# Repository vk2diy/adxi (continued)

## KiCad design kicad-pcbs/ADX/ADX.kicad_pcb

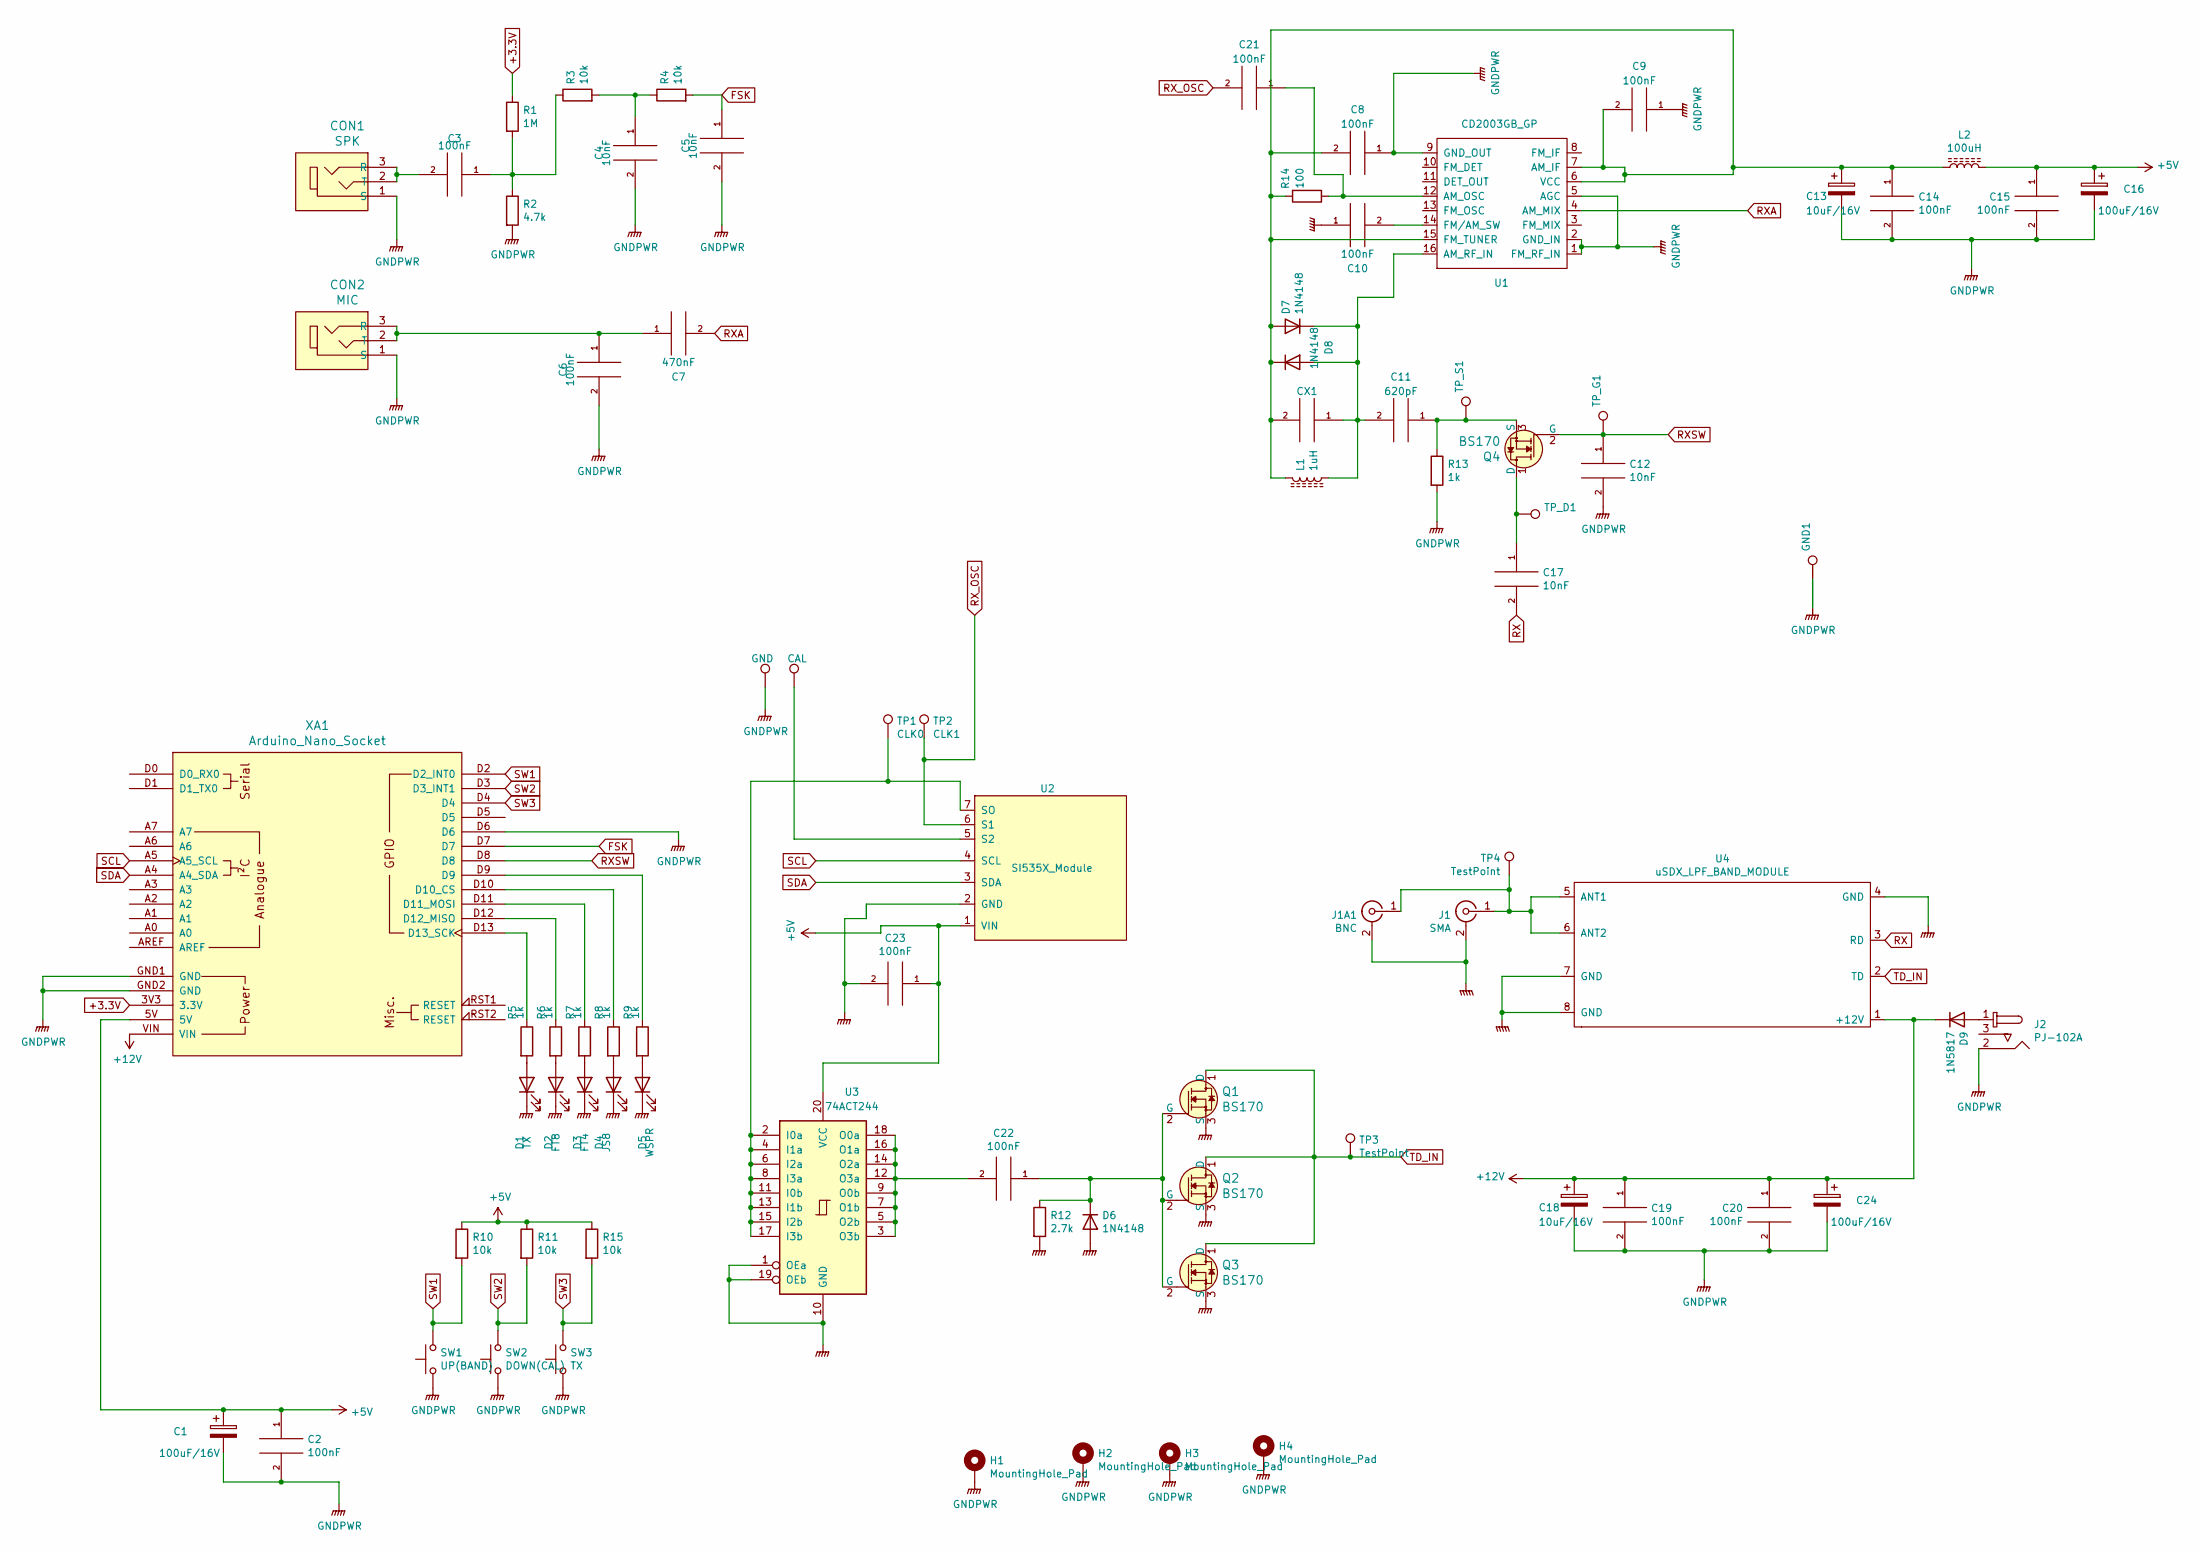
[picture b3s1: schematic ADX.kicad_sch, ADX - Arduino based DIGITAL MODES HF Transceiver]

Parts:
C1, C16, C24: 100uF/16V; CP_Radial_D5.0mm_P2.50mm
C2, C3, C6, C8, C9, C10, C14, C15, C19, C20, C21, C22, C23: 100nF; C_Disc_D3.0mm_W1.6mm_P2.50mm
C4, C5: 10nF; C_Disc_D3.0mm_W1.6mm_P2.50mm
C7: 470nF; C_Disc_D3.0mm_W1.6mm_P2.50mm
C11: 620pF; C_Disc_D3.0mm_W1.6mm_P2.50mm
C12, C17: 10nF; C_Disc_D3.0mm_W2.0mm_P2.50mm
C13, C18: 10uF/16V; CP_Radial_D5.0mm_P2.50mm
CON1: SPK; Headphone_Jack_3.5mm_SJ1-3523N; MPN SJ1-3523N; Digi-Key_PN CP1-3523N-ND
CON2: MIC; Headphone_Jack_3.5mm_SJ1-3523N; MPN SJ1-3523N; Digi-Key_PN CP1-3523N-ND
CX1: C_Disc_D3.0mm_W1.6mm_P2.50mm
D1: TX; LED_D3.0mm
D2: FT8; LED_D3.0mm
D3: FT4; LED_D3.0mm
D4: JS8; LED_D3.0mm
D5: WSPR; LED_D3.0mm
D6: 1N4148; D_A-405_P2.54mm_Vertical_AnodeUp
D7, D8: 1N4148; D_A-405_P2.54mm_Vertical_KathodeUp
D9: 1N5817; D_A-405_P2.54mm_Vertical_KathodeUp
GND1: TestPoint_THTPad_2.0x2.0mm_Drill1.0mm
H1, H2, H3, H4: MountingHole_Pad; MountingHole_3.2mm_M3_ISO7380_Pad
J1: SMA; SMA_Samtec_SMA-J-P-X-ST-EM1_EdgeMount
J1A1: BNC; BNC_Amphenol_B6252HB-NPP3G-50_Horizontal
J2: PJ-102A; Barrel_Jack_5.5mmODx2.1mmID_PJ-102A; MPN PJ-102A; Digi-Key_PN CP-102A-ND
L1: 1uH; L_Toroid_Vertical_L10.0mm_W5.0mm_P5.08mm
L2: 100uH; R_Axial_DIN0204_L3.6mm_D1.6mm_P2.54mm_Vertical
Q1, Q2, Q3: BS170; TO-92_HandSolder; MPN BS170; Digi-Key_PN BS170-ND
Q4: BS170; TO-92L_HandSolder; MPN BS170; Digi-Key_PN BS170-ND
R1: 1M; R_Axial_DIN0204_L3.6mm_D1.6mm_P1.90mm_Vertical
R2: 4.7k; R_Axial_DIN0204_L3.6mm_D1.6mm_P1.90mm_Vertical
R3, R4, R10, R11, R15: 10k; R_Axial_DIN0204_L3.6mm_D1.6mm_P1.90mm_Vertical
R5, R6, R7, R8, R9, R13: 1k; R_Axial_DIN0204_L3.6mm_D1.6mm_P1.90mm_Vertical
R12: 2.7k; R_Axial_DIN0204_L3.6mm_D1.6mm_P1.90mm_Vertical
R14: 100; R_Axial_DIN0204_L3.6mm_D1.6mm_P1.90mm_Vertical
SW1: UP(BAND); SW_PUSH_6mm
SW2: DOWN(CAL); SW_PUSH_6mm
SW3: TX; SW_PUSH_6mm
TP1: CLK0; TestPoint_THTPad_2.0x2.0mm_Drill1.0mm
TP2: CLK1; TestPoint_THTPad_2.0x2.0mm_Drill1.0mm
TP3, TP4: TestPoint; TestPoint_THTPad_2.0x2.0mm_Drill1.0mm
TP7: GND; TestPoint_THTPad_2.0x2.0mm_Drill1.0mm
TP8: CAL; TestPoint_THTPad_2.0x2.0mm_Drill1.0mm
TP_D1: TestPoint_THTPad_1.0x1.0mm_Drill0.5mm
TP_G1: TestPoint_THTPad_1.0x1.0mm_Drill0.5mm
TP_S1: TestPoint_THTPad_1.0x1.0mm_Drill0.5mm
U1: CD2003GB_GP; DIP-16_W7.62mm_Socket_LongPads
U2: SI535X_Module; SI5351 Module_Vertical
U3: 74ACT244; DIP-20_W7.62mm_LongPads
U4: uSDX_LPF_BAND_MODULE; uSDX_LPF_Band_Module
XA1: Arduino_Nano_Socket

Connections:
+3.3V: R1.1, XA1.3V3 (3.3V)
+5V: C1.1, C2.1, C15.1, C16.1, C23.1, L2.1, R10.1, R11.1, R15.1, U2.1 (VIN), U3.20 (VCC), XA1.5V
+12V: C18.1, C19.1, C20.1, C24.1, D9.1 (K), U4.1 (+12V), XA1.VIN
FSK: C5.1, R4.2, XA1.D7
GNDPWR: C1.2, C2.2, C4.2, C5.2, C6.2, C8.1, C9.1, C10.1, C12.2, C13.2, C14.2, C15.2, C16.2, C18.2, C19.2, C20.2, C23.2, C24.2, CON1.1 (S), CON2.1 (S), D1.1 (K), D2.1 (K), D3.1 (K), D4.1 (K), D5.1 (K), D6.2 (A), GND1.1, H1.1, H2.1, H3.1, H4.1, J1.2 (Ext), J1A1.2 (Ext), J2.2, Q1.3 (S), Q2.3 (S), Q3.3 (S), R2.2, R12.2, R13.2, SW1.1, SW2.1, SW3.1, TP7.1, U1.1 (FM_RF_IN), U1.2 (GND_IN), U1.5 (AGC), U1.9 (GND_OUT), U2.2 (GND), U3.1 (OEa), U3.10 (GND), U3.19 (OEb), U4.4 (GND), U4.7 (GND), U4.8 (GND), XA1.D6, XA1.GND1 (GND), XA1.GND2 (GND)
unnamed: C3.1, R1.2, R2.1, R3.1
unnamed: C3.2, CON1.2 (T), CON1.3 (R)
unnamed: C4.1, R3.2, R4.1
unnamed: C6.1, C7.1, CON2.2 (T), CON2.3 (R)
unnamed: C10.2, U1.14 (FM/AM_SW)
unnamed: C11.1, Q4.3 (S), R13.1, TP_S1.1
unnamed: C11.2, CX1.1, D7.1 (K), D8.2 (A), L1.1, U1.16 (AM_RF_IN)
unnamed: C8.2, C9.2, C13.1, C14.1, CX1.2, D7.2 (A), D8.1 (K), L1.2, L2.2, R14.2, U1.6 (VCC), U1.7 (AM_IF), U1.15 (FM_TUNER)
unnamed: C17.1, Q4.1 (D), TP_D1.1
unnamed: C21.1, R14.1, U1.12 (AM_OSC)
unnamed: C22.1, D6.1 (K), Q1.2 (G), Q2.2 (G), Q3.2 (G), R12.1
unnamed: C22.2, U3.3 (O3b), U3.5 (O2b), U3.7 (O1b), U3.9 (O0b), U3.12 (O3a), U3.14 (O2a), U3.16 (O1a), U3.18 (O0a)
unnamed: D1.2 (A), R5.2
unnamed: D2.2 (A), R6.2
unnamed: D3.2 (A), R7.2
unnamed: D4.2 (A), R8.2
unnamed: D5.2 (A), R9.2
unnamed: D9.2 (A), J2.1
unnamed: J1.1 (In), J1A1.1 (In), TP4.1, U4.5 (ANT1), U4.6 (ANT2)
unnamed: R5.1, XA1.D13 (D13_SCK)
unnamed: R6.1, XA1.D12 (D12_MISO)
unnamed: R7.1, XA1.D11 (D11_MOSI)
unnamed: R8.1, XA1.D10 (D10_CS)
unnamed: R9.1, XA1.D9
unnamed: TP1.1, U2.7 (SO), U3.2 (I0a), U3.4 (I1a), U3.6 (I2a), U3.8 (I3a), U3.11 (I0b), U3.13 (I1b), U3.15 (I2b), U3.17 (I3b)
unnamed: TP8.1, U2.5 (S2)
RX: C17.2, U4.3 (RD)
RXA: C7.2, U1.4 (AM_MIX)
RXSW: C12.1, Q4.2 (G), TP_G1.1, XA1.D8
RX_OSC: C21.2, TP2.1, U2.6 (S1)
SCL: U2.4 (SCL), XA1.A5 (A5_SCL)
SDA: U2.3 (SDA), XA1.A4 (A4_SDA)
SW1: R10.2, SW1.2, XA1.D2 (D2_INT0)
SW2: R11.2, SW2.2, XA1.D3 (D3_INT1)
SW3: R15.2, SW3.2, XA1.D4
TD_IN: Q1.1 (D), Q2.1 (D), Q3.1 (D), TP3.1, U4.2 (TD)

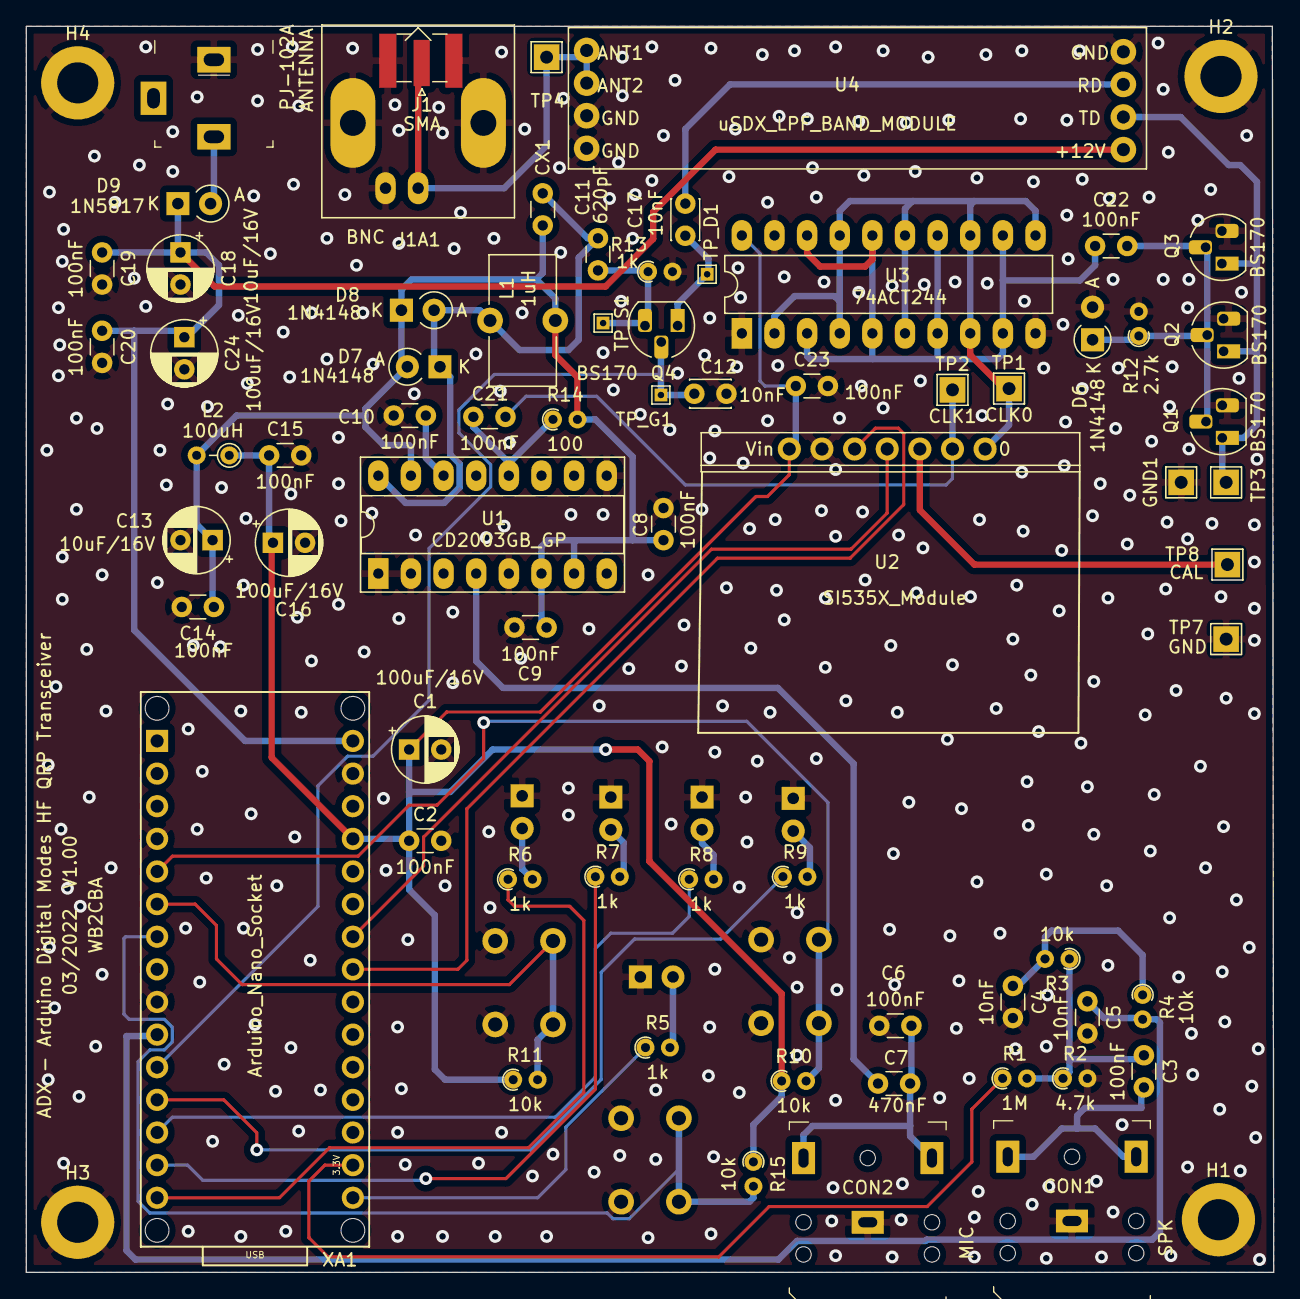
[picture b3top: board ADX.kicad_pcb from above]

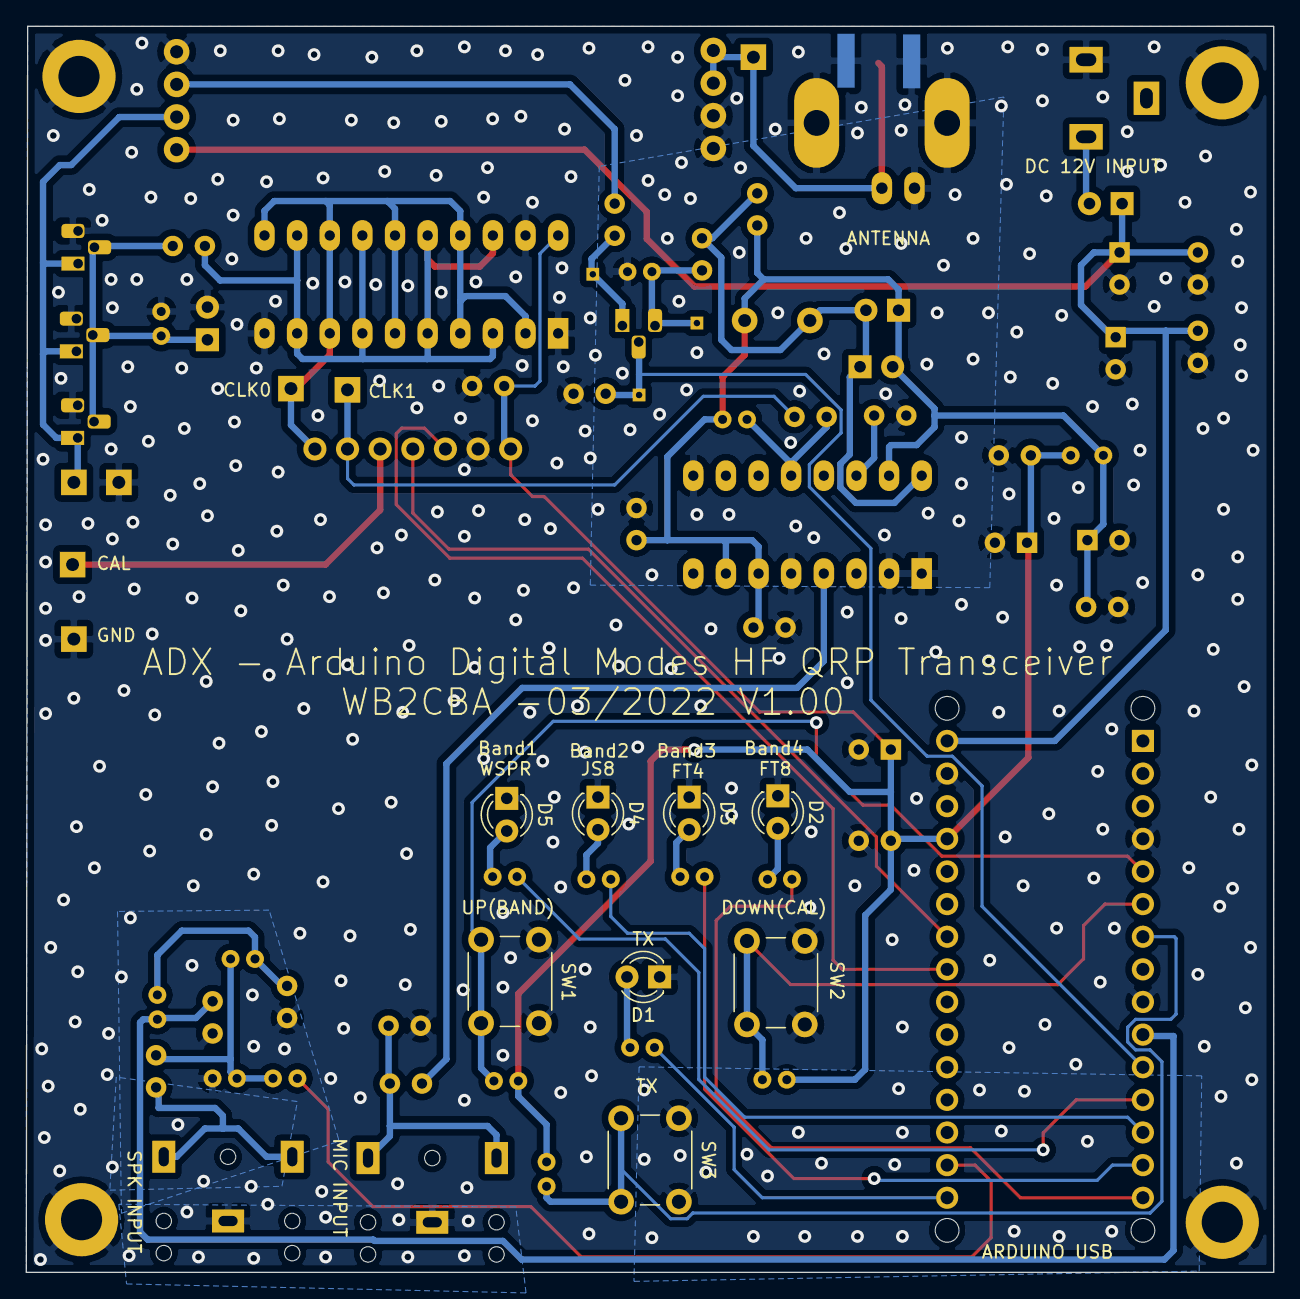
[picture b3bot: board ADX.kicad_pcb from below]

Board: 2 copper layers, 97.1 x 97.0 mm, 82 parts (8 on the bottom side), 41 nets.

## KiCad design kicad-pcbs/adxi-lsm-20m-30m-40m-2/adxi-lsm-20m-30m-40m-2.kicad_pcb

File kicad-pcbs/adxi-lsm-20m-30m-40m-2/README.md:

# adxi-lsm-20m-30m-40m-2

## Timeline

 * Conceived: 2024-10-01 or so
 * Designed: 2024-10-01 to 2024-10-24
   * Main design challenges were re-working existing designs coming out of [classe2-calculator](https://github.com/vk2diy/classe2-calculator)
   * The rework function `--equivalent-inductor` had to be authored and debugged
   * The reworked circuits are definitely better than the originals
 * Ordered: 2024-10-24
   * Cost: $17.80 for 20 boards + $98.70 for 20 boards assembly = $116.5 / 20 = $5.825 each
 * ETA: 2024-11-05 or so

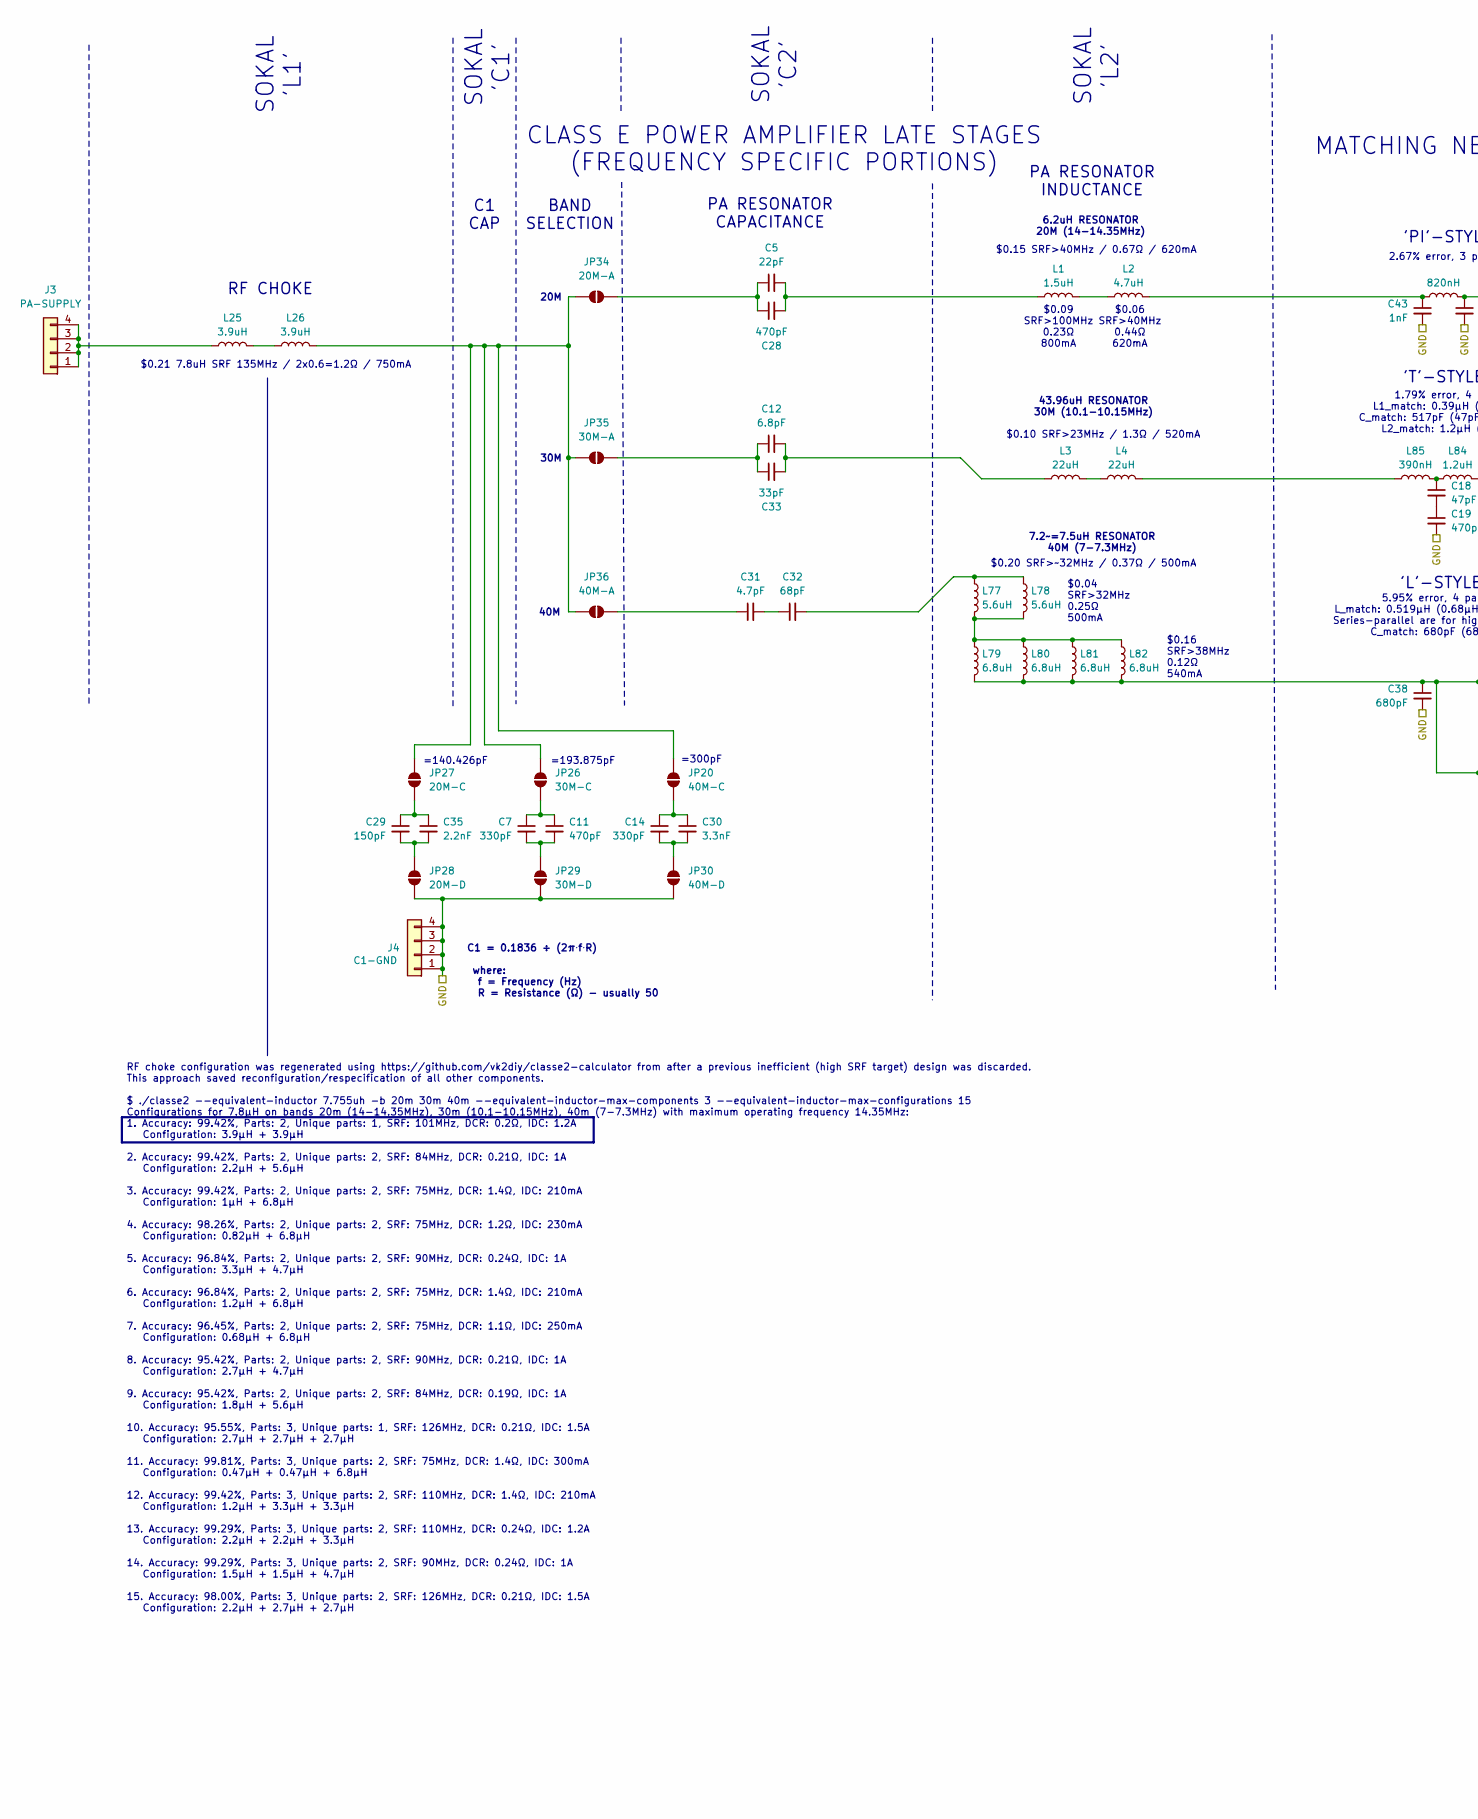
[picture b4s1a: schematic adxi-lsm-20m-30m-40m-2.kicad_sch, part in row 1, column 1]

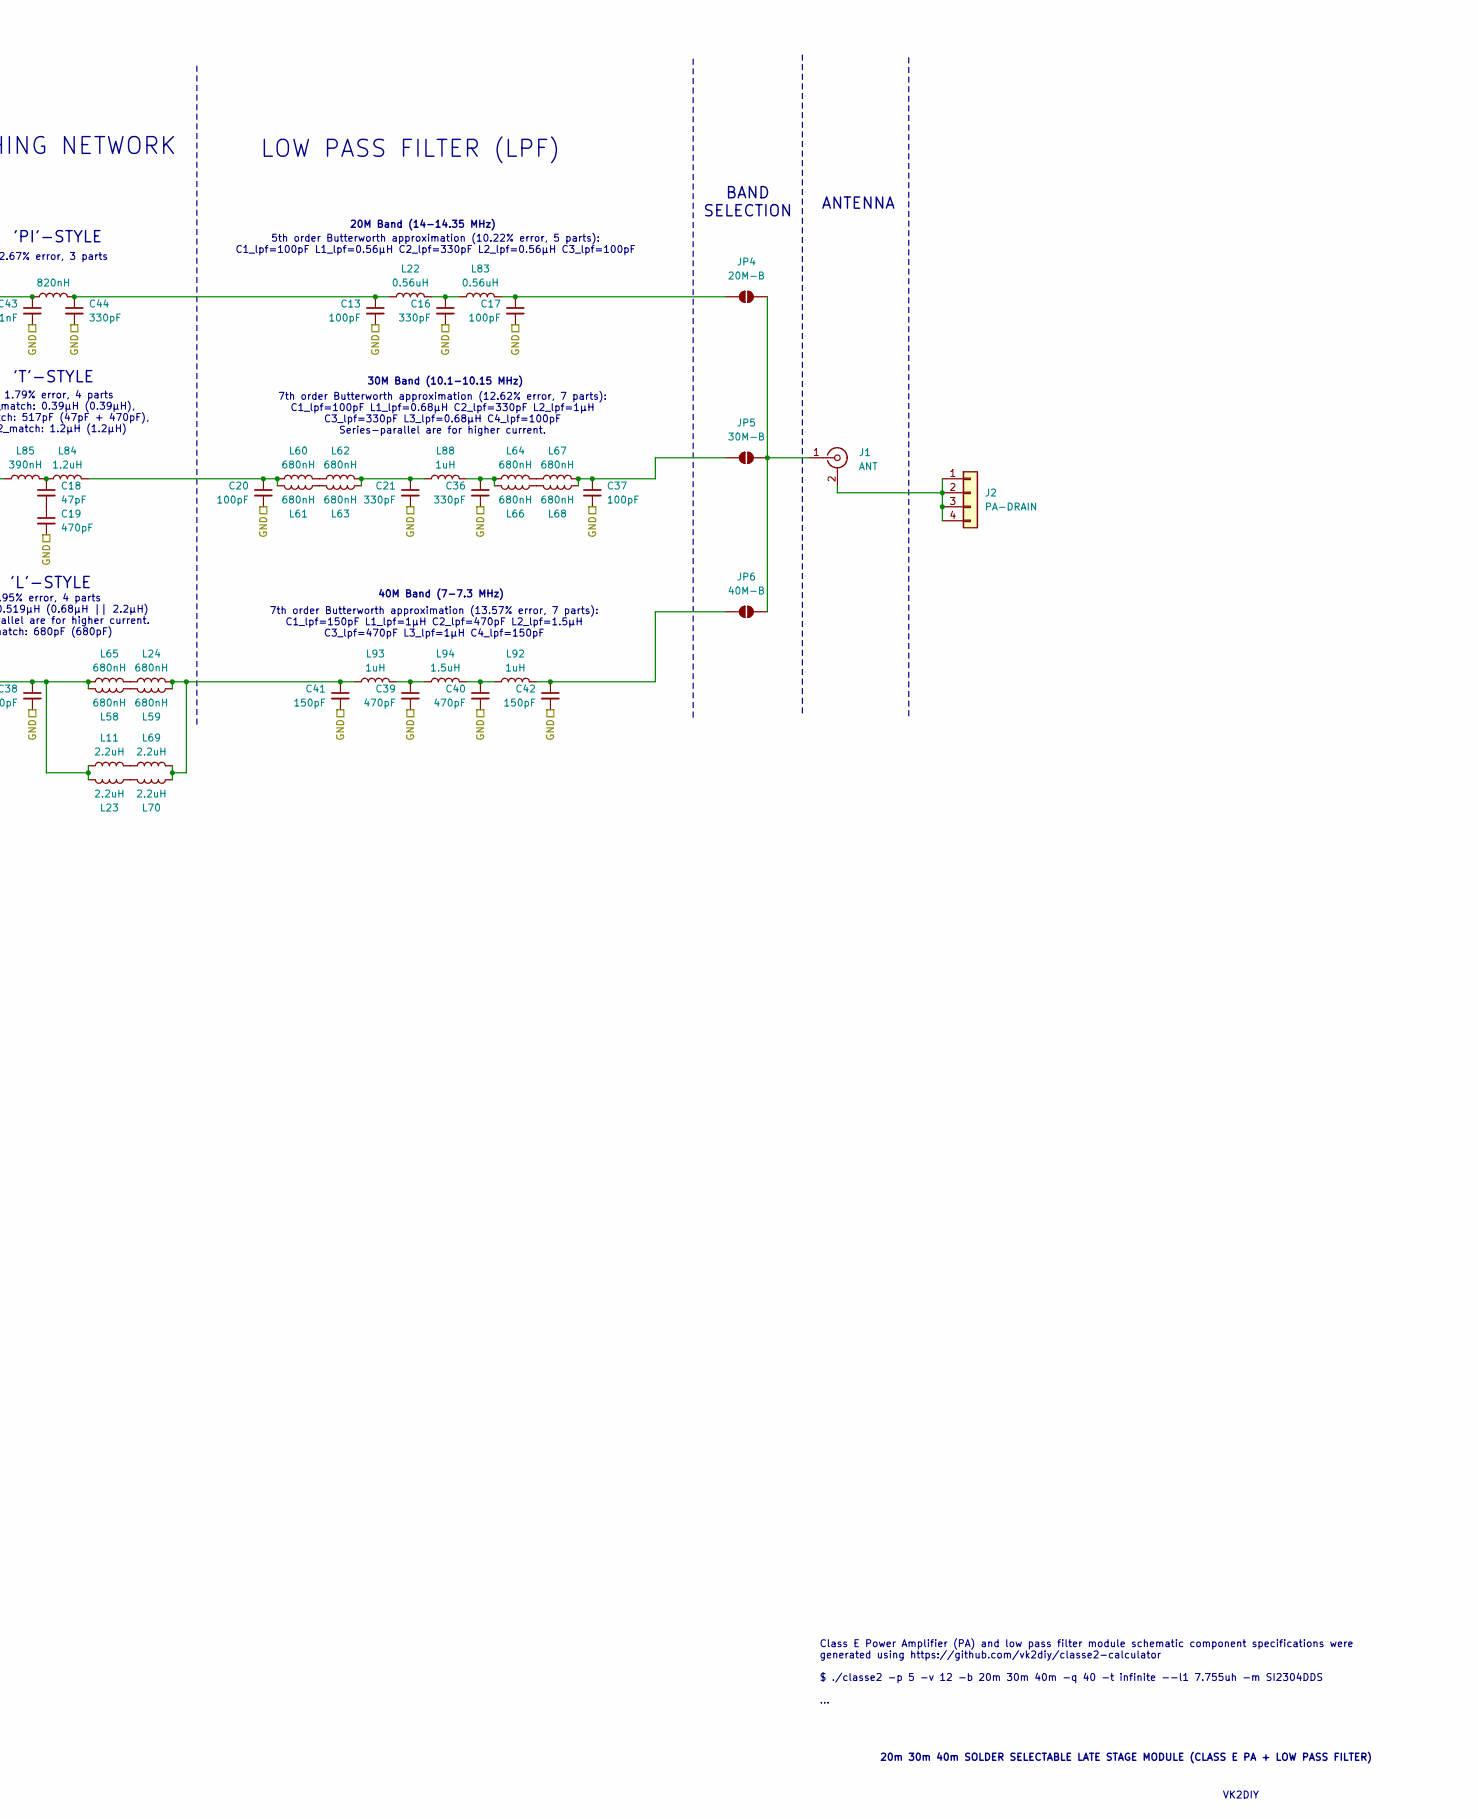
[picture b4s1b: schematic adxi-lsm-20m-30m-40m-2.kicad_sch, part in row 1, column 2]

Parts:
C5: 22pF; C_0805_2012Metric; MPN CL21C220JBANNNC; LCSC Part # C1804
C7, C14, C16, C21, C36, C44: 330pF; C_0603_1608Metric; MPN CL10C331JB8NNNC; LCSC Part # C1664
C11: 470pF; C_0603_1608Metric; MPN 0603B471K500NT; LCSC Part # C1620
C12: 6.8pF; C_0603_1608Metric; MPN 0603CG6R8C500NT; LCSC Part # C1679
C13, C17, C20, C37: 100pF; C_0805_2012Metric; MPN CL21C101JBANNNC; LCSC Part # C1790
C18: 47pF; C_0805_2012Metric; MPN CL21C470JBANNNC; LCSC Part # C14857
C19, C39, C40: 470pF; C_0805_2012Metric; MPN 0805B471K500NT; LCSC Part # C1743
C28: 470pF; C_0603_1608Metric; MPN CC0603JRNPO9BN471; LCSC Part # C106211
C29, C41, C42: 150pF; C_0603_1608Metric; MPN 0603B151K500NT; LCSC Part # C1594
C30: 3.3nF; C_0603_1608Metric; MPN CL10B332KB8NNNC; LCSC Part # C1613
C31: 4.7pF; C_0603_1608Metric; MPN 0603CG4R7C500NT; LCSC Part # C1669
C32: 68pF; C_0603_1608Metric; MPN CL10C680JB8NNNC; LCSC Part # C28262
C33: 33pF; C_1206_3216Metric; MPN GRM31A5C2J330JW01D; LCSC Part # C415521
C35: 2.2nF; C_0805_2012Metric; MPN CL21C222JBFNNNE; LCSC Part # C28260
C38: 680pF; C_0805_2012Metric; MPN CC0805JRNPO9BN681; LCSC Part # C107121
C43: 1nF; C_1206_3216Metric; MPN 1206B102K202NT; LCSC Part # C9196
J1: ANT; ANT-TH_KH-BNC50-3511
J2: PA-DRAIN; PinSocket_1x04_P2.54mm_Vertical
J3: PA-SUPPLY; PinSocket_1x04_P2.54mm_Vertical
J4: C1-GND; PinSocket_1x04_P2.54mm_Vertical
JP4: 20M-B; SolderJumper-2_P1.3mm_Open_RoundedPad1.0x1.5mm
JP5: 30M-B; SolderJumper-2_P1.3mm_Open_RoundedPad1.0x1.5mm
JP6: 40M-B; SolderJumper-2_P1.3mm_Open_RoundedPad1.0x1.5mm
JP20: 40M-C; SolderJumper-2_P1.3mm_Open_RoundedPad1.0x1.5mm
JP26: 30M-C; SolderJumper-2_P1.3mm_Open_RoundedPad1.0x1.5mm
JP27: 20M-C; SolderJumper-2_P1.3mm_Open_RoundedPad1.0x1.5mm
JP28: 20M-D; SolderJumper-2_P1.3mm_Open_RoundedPad1.0x1.5mm
JP29: 30M-D; SolderJumper-2_P1.3mm_Open_RoundedPad1.0x1.5mm
JP30: 40M-D; SolderJumper-2_P1.3mm_Open_RoundedPad1.0x1.5mm
JP34: 20M-A; SolderJumper-2_P1.3mm_Open_RoundedPad1.0x1.5mm
JP35: 30M-A; SolderJumper-2_P1.3mm_Open_RoundedPad1.0x1.5mm
JP36: 40M-A; SolderJumper-2_P1.3mm_Open_RoundedPad1.0x1.5mm
L1, L94: 1.5uH; L_0603_1608Metric; MPN LQM18PN1R5MFRL; LCSC Part # C337909
L2: 4.7uH; L_0603_1608Metric; MPN LQM18PN4R7MFRL; LCSC Part # C114862
L3, L4: 22uH; L_Sunlord_SWPA3015S; MPN SWPA3015S220MT; LCSC Part # C83438
L11, L23, L69, L70: 2.2uH; L_0603_1608Metric; MPN LS0603-2R2J-N; LCSC Part # C2935084
L22, L83: 0.56uH; L_0805_2012Metric; MPN FHW0805UFR56JST; LCSC Part # C304279
L24, L58, L59, L60, L61, L62, L63, L64, L65, L66, L67, L68: 680nH; L_0603_1608Metric; MPN CMH160808BR68MT; LCSC Part # C394955
L25, L26: 3.9uH; L_1812_4532Metric; MPN FHW1812IF3R9JST; LCSC Part # C394117
L77, L78: 5.6uH; L_0805_2012Metric; MPN CMP201209XD5R6MT; LCSC Part # C395017
L79, L80, L81, L82: 6.8uH; L_0805_2012Metric; MPN LB2012T6R8M; LCSC Part # C223247
L84: 1.2uH; L_0805_2012Metric; MPN YWLD2012-1R2K; LCSC Part # C5563768
L85: 390nH; L_0603_1608Metric; MPN LCF0603-R39J-T; LCSC Part # C251955
L88, L92, L93: 1uH; L_1812_4532Metric; MPN CMI453215U1R0KT; LCSC Part # C75658
L90: 820nH; L_0805_2012Metric; MPN FHW0805UFR82JST; LCSC Part # C393988

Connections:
/GND: C13.2, C16.2, C17.2, C19.2, C20.2, C21.2, C36.2, C37.2, C38.2, C39.2, C40.2, C41.2, C42.2, C43.2, C44.2, J4.1, J4.2, J4.3, J4.4, JP28.1 (A), JP29.1 (A), JP30.1 (A)
unnamed: C12.2, C33.2, L3.1
unnamed: C13.1, C44.1, L22.1, L90.2
unnamed: C16.1, L22.2, L83.1
unnamed: C18.1, L84.1, L85.2
unnamed: C18.2, C19.1
unnamed: C20.1, L60.1, L61.1, L84.2
unnamed: C21.1, L62.2, L63.2, L88.1
unnamed: C5.2, C28.2, L1.1
unnamed: C31.2, C32.1
unnamed: C32.2, L77.1, L78.1
unnamed: C36.1, L64.1, L66.1, L88.2
unnamed: C38.1, L11.1, L23.1, L58.1, L65.1, L79.2, L80.2, L81.2, L82.2
unnamed: C39.1, L93.2, L94.1
unnamed: C40.1, L92.1, L94.2
unnamed: C41.1, L24.2, L59.2, L69.2, L70.2, L93.1
unnamed: C43.1, L2.2, L90.1
unnamed: J1.2 (Ext), J2.1, J2.2, J2.3, J2.4
unnamed: J1.1 (In), JP4.2 (B), JP5.2 (B), JP6.2 (B)
unnamed: J3.1, J3.2, J3.3, J3.4, L25.1
unnamed: C17.1, JP4.1 (A), L83.2
unnamed: C37.1, JP5.1 (A), L67.2, L68.2
unnamed: C42.1, JP6.1 (A), L92.2
unnamed: C14.1, C30.1, JP20.1 (A)
unnamed: JP20.2 (B), JP26.2 (B), JP27.2 (B), JP34.1 (A), JP35.1 (A), JP36.1 (A), L26.2
unnamed: C7.1, C11.1, JP26.1 (A)
unnamed: C29.1, C35.1, JP27.1 (A)
unnamed: C29.2, C35.2, JP28.2 (B)
unnamed: C7.2, C11.2, JP29.2 (B)
unnamed: C14.2, C30.2, JP30.2 (B)
unnamed: C5.1, C28.1, JP34.2 (B)
unnamed: C12.1, C33.1, JP35.2 (B)
unnamed: C31.1, JP36.2 (B)
unnamed: L1.2, L2.1
unnamed: L3.2, L4.1
unnamed: L4.2, L85.1
unnamed: L11.2, L69.1
unnamed: L23.2, L70.1
unnamed: L24.1, L65.2
unnamed: L25.2, L26.1
unnamed: L58.2, L59.1
unnamed: L60.2, L62.1
unnamed: L61.2, L63.1
unnamed: L64.2, L67.1
unnamed: L66.2, L68.1
unnamed: L77.2, L78.2, L79.1, L80.1, L81.1, L82.1

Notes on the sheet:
RF CHOKE
20m 30m 40m SOLDER SELECTABLE LATE STAGE MODULE (CLASS E PA + LOW PASS FILTER)
7th order Butterworth approximation (13.57% error, 7 parts): C1_lpf=150pF L1_lpf=1µH C2_lpf=470pF L2_lpf=1.5µH C3_lpf=470pF L3_lpf=1µH C4_lpf=150pF
RF choke configuration was regenerated using https://github.com/vk2diy/classe2-calculator from after a previous inefficient (high SRF target) design was discarded. This approach saved reconfiguration/respecification of all other components. $ ./classe2 --equivalent-inductor 7.755uh -b 20m 30m 40m -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
$0.10 SRF>23MHz / 1.3Ω / 520mA
6.2uH RESONATOR 20M (14-14.35MHz)
2.67% error, 3 parts
5th order Butterworth approximation (10.22% error, 5 parts): C1_lpf=100pF L1_lpf=0.56µH C2_lpf=330pF L2_lpf=0.56µH C3_lpf=100pF
30M
ANTENNA
20M Band (14-14.35 MHz)
=140.426pF
40M Band (7-7.3 MHz)
$0.21 7.8uH SRF 135MHz / 2x0.6=1.2Ω / 750mA
$0.09 SRF>100MHz 0.23Ω 800mA
$0.06 SRF>40MHz 0.44Ω 620mA
'PI'-STYLE
Class E Power Amplifier (PA) and low pass filter module schematic component specifications were generated using https://github.com/vk2diy/classe2-calculator $ ./classe2 -p 5 -v 12 -b 20m 30m 40m -q 40 -t infinite --l1 7.755uh -m SI2304DDS ...
C1 = 0.1836 ÷ (2π⋅f⋅R) where: f = Frequency (Hz) R = Resistance (Ω) - usually 50
LOW PASS FILTER (LPF)
5.95% error, 4 parts L_match: 0.519µH (0.68µH || 2.2µH) Series-parallel are for higher current. C_match: 680pF (680pF)
$0.04 SRF>32MHz 0.25Ω 500mA
'T'-STYLE
1.79% error, 4 parts L1_match: 0.39µH (0.39µH), C_match: 517pF (47pF + 470pF), L2_match: 1.2µH (1.2µH)
VK2DIY
BAND SELECTION
'L'-STYLE
MATCHING NETWORK
20M
=300pF
C1 CAP
SOKAL 'C2'
$0.15 SRF>40MHz / 0.67Ω / 620mA
30M Band (10.1-10.15 MHz)
43.96uH RESONATOR 30M (10.1-10.15MHz)
$0.16 SRF>38MHz 0.12Ω 540mA
SOKAL 'L1'
7.2~=7.5uH RESONATOR 40M (7-7.3MHz)
PA RESONATOR INDUCTANCE
SOKAL 'L2'

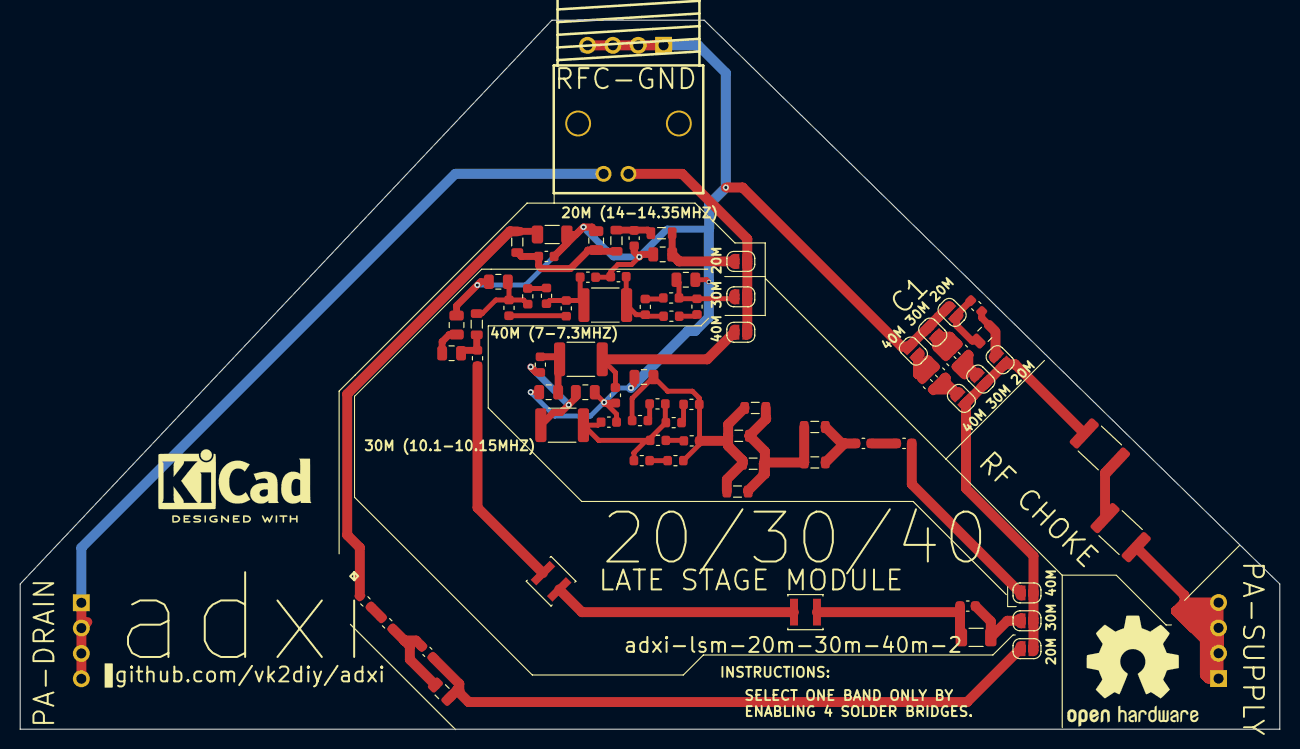
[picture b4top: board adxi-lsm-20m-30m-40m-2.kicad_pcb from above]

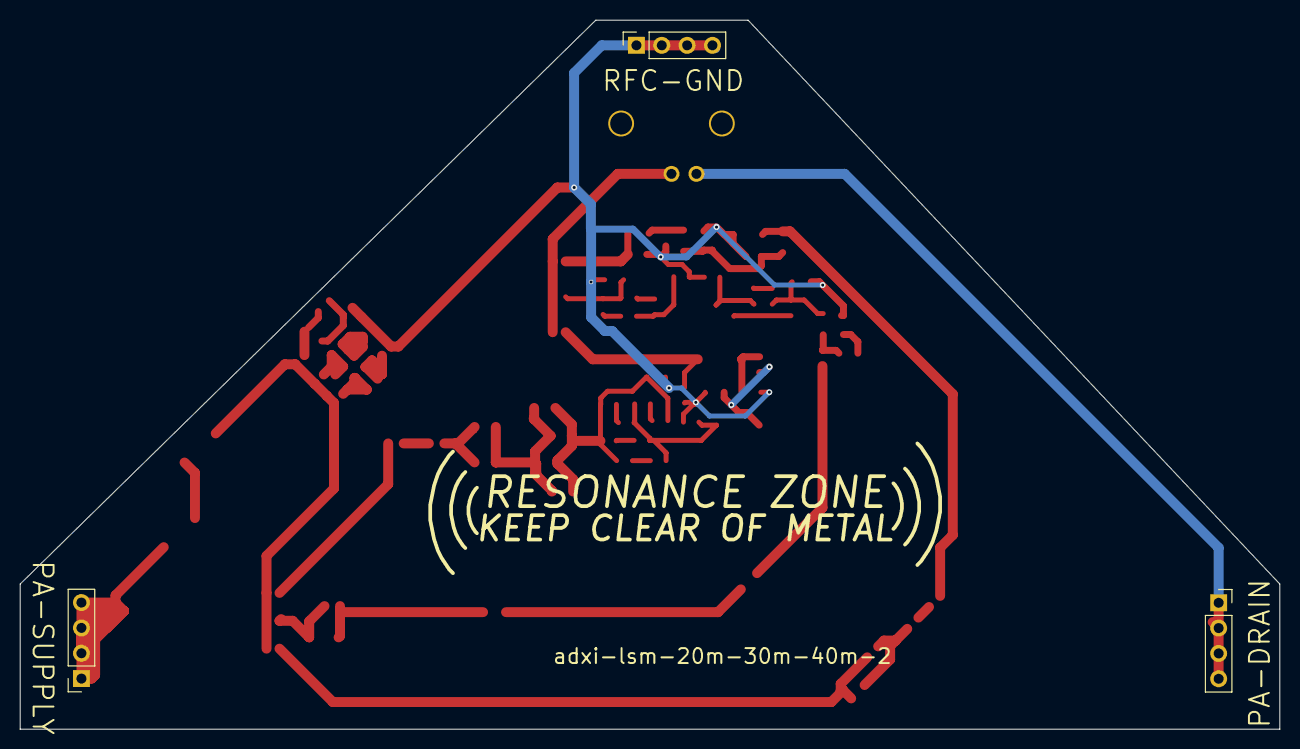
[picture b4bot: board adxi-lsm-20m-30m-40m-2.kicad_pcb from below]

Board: 2 copper layers, 126.3 x 71.1 mm, 81 parts (3 on the bottom side), 46 nets.
